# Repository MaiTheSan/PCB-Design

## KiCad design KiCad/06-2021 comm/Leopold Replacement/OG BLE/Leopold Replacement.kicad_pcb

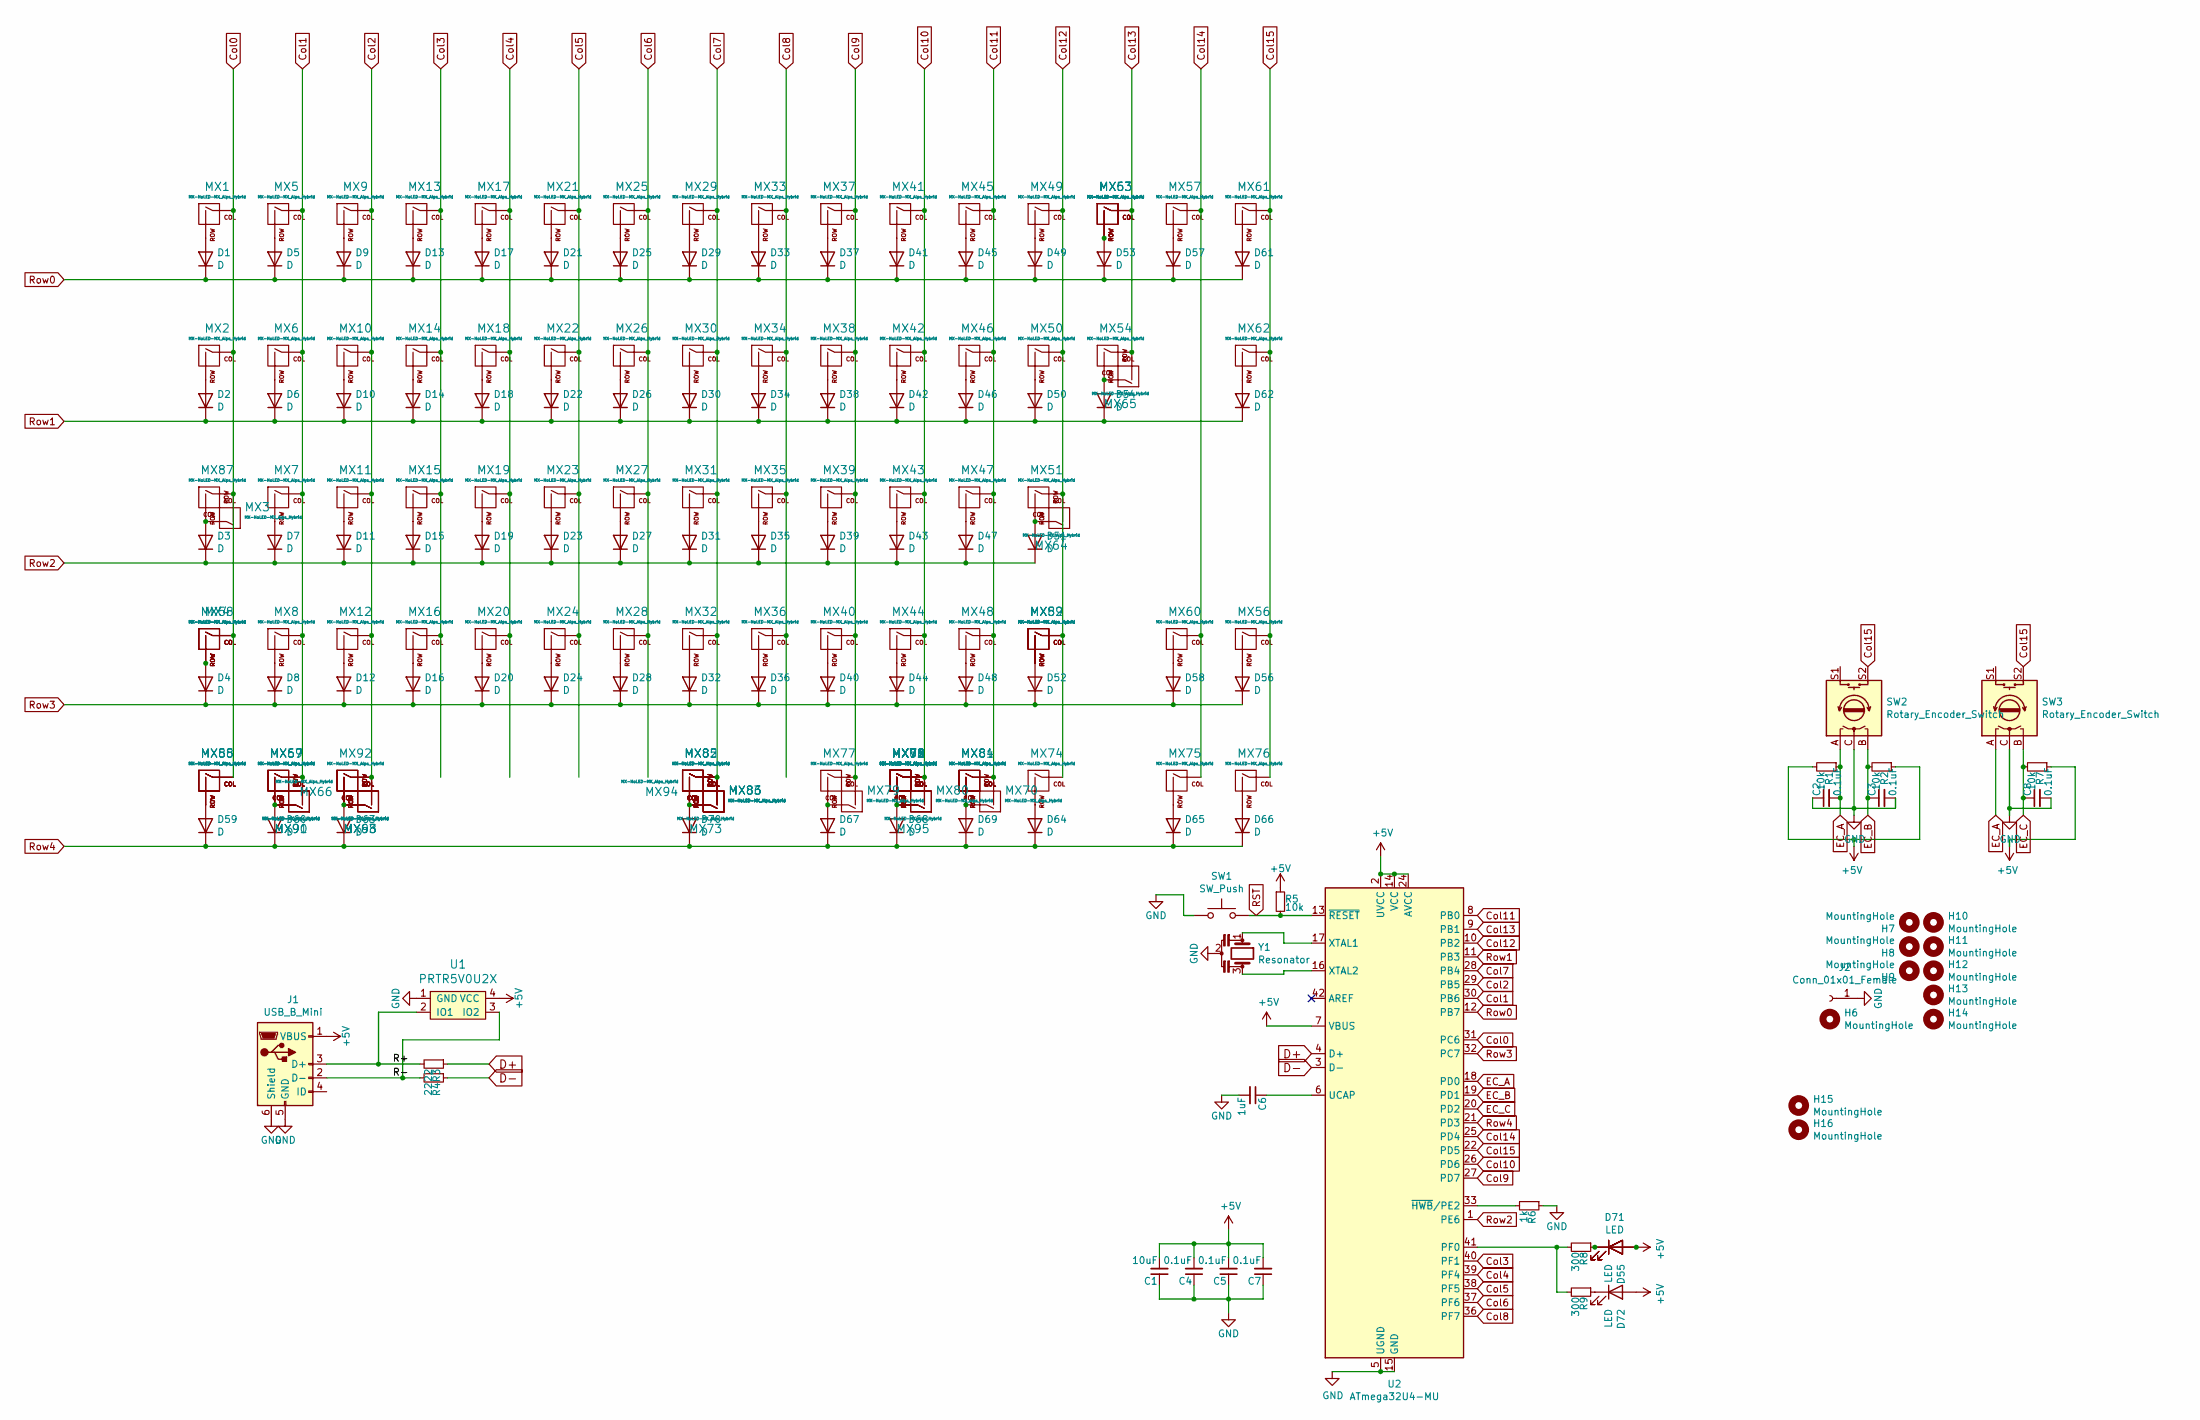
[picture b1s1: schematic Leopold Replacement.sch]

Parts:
C1: 10uF; C_0603
C2, C3, C4, C5, C7, C8: 0.1uF; C_0603
C6: 1uF; C_0603
D1, D2, D3, D4, D5, D6, D7, D8, D9, D10, D11, D12, D13, D14, D15, D16, D17, D18, D19, D20, D21, D22, D23, D24, D25, D26, D27, D28, D29, D30, D31, D32, D33, D34, D35, D36, D37, D38, D39, D40, D41, D42, D43, D44, D45, D46, D47, D48, D49, D50, D51, D52, D53, D54, D56, D57, D58, D59, D60, D61, D62, D63, D64, D65, D66, D67, D68, D69, D70: D; D_SOD-123
D55: LED; MXOnly-LEDONLY
D71: LED; MXOnly-LEDONLY-FLIPPED
D72: LED; MXOnly-LEDONLY-MID
H6: MountingHole; 10mm-Leopold-Mounting-Hole
H7, H8, H9, H10, H11, H12, H13, H14: MountingHole; Leopold-Mounting-Hole-Main
H15, H16: MountingHole; Leopold-mounting-hole-circle
J1: USB_B_Mini; Molex-0548190589
J2: Conn_01x01_Female; Leopold-Mounting-Hole
MX1, MX2, MX3, MX5, MX6, MX7, MX8, MX9, MX10, MX11, MX12, MX13, MX14, MX15, MX16, MX17, MX18, MX19, MX20, MX21, MX22, MX23, MX24, MX25, MX26, MX27, MX28, MX29, MX30, MX31, MX32, MX33, MX34, MX35, MX36, MX37, MX38, MX39, MX40, MX41, MX42, MX43, MX44, MX45, MX46, MX47, MX48, MX49, MX50, MX53, MX54, MX56, MX57, MX58, MX60, MX61, MX62, MX65, MX67, MX74, MX75, MX76, MX81, MX89, MX91: MX-NoLED-MX_Alps_Hybrid; Mx_Alps_100
MX4, MX51, MX52, MX64: MX-NoLED-MX_Alps_Hybrid; Mx_Alps_225
MX55, MX59, MX66, MX68, MX77, MX78, MX79, MX80, MX84, MX87: MX-NoLED-MX_Alps_Hybrid; Mx_Alps_125
MX63: MX-NoLED-MX_Alps_Hybrid; Mx_Alps_200
MX69, MX70, MX71, MX92, MX95: MX-NoLED-MX_Alps_Hybrid; ALPS-1.5U
MX72, MX88, MX93, MX96: MX-NoLED-MX_Alps_Hybrid; Mx_Alps_150
MX73, MX85: MX-NoLED-MX_Alps_Hybrid; ALPS-6.5U
MX82, MX83: MX-NoLED-MX_Alps_Hybrid; Mx_Alps_625_FL
MX86, MX94: MX-NoLED-MX_Alps_Hybrid; Mx_Alps_700_FL
MX90: MX-NoLED-MX_Alps_Hybrid; ALPS-1.25U
R1, R2, R5, R7: 10k; R_0805
R3, R4: 22; R_0603
R6: 1k; R_0805
R8, R9: 300; R_0805
SW1: SW_Push; SKQG-1155865
SW2, SW3: Rotary_Encoder_Switch; RotaryEncoder_Alps_EC11E-Switch_Vertical_H20mm_Center
U1: PRTR5V0U2X; SOT143B
U2: ATmega32U4-MU; QFN-44-1EP_7x7mm_P0.5mm_EP5.15x5.15mm
Y1: Resonator; Resonator_SMD_muRata_CSTxExxV-3Pin_3.0x1.1mm

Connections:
+5V: C1.2, C4.2, C5.2, C7.2, D55.2 (A), D71.2 (A), D72.2 (A), J1.1 (VBUS), R1.2, R2.1, R5.1, R7.1, U1.4 (VCC), U2.2 (UVCC), U2.7 (VBUS), U2.14 (VCC), U2.24 (AVCC), U2.34 (VCC), U2.44 (AVCC)
/R+: J1.3 (D+), R3.2, U1.2 (IO1)
/R-: J1.2 (D-), R4.2, U1.3 (IO2)
Col0: MX1.1 (COL), MX2.1 (COL), MX3.2 (ROW), MX4.1 (COL), MX55.1 (COL), MX58.1 (COL), MX87.1 (COL), MX88.1 (COL), U2.31 (PC6)
Col1: MX5.1 (COL), MX6.1 (COL), MX7.1 (COL), MX8.1 (COL), MX59.1 (COL), MX67.1 (COL), MX90.2 (ROW), MX91.2 (ROW), U2.30 (PB6)
Col2: MX9.1 (COL), MX10.1 (COL), MX11.1 (COL), MX12.1 (COL), MX66.1 (COL), MX68.2 (ROW), MX92.1 (COL), MX93.2 (ROW), U2.29 (PB5)
Col3: MX13.1 (COL), MX14.1 (COL), MX15.1 (COL), MX16.1 (COL), U2.40 (PF1)
Col4: MX17.1 (COL), MX18.1 (COL), MX19.1 (COL), MX20.1 (COL), U2.39 (PF4)
Col5: MX21.1 (COL), MX22.1 (COL), MX23.1 (COL), MX24.1 (COL), U2.38 (PF5)
Col6: MX25.1 (COL), MX26.1 (COL), MX27.1 (COL), MX28.1 (COL), U2.37 (PF6)
Col7: MX29.1 (COL), MX30.1 (COL), MX31.1 (COL), MX32.1 (COL), MX73.2 (ROW), MX82.1 (COL), MX83.2 (ROW), MX85.1 (COL), MX86.2 (ROW), MX94.1 (COL), U2.28 (PB4)
Col8: MX33.1 (COL), MX34.1 (COL), MX35.1 (COL), MX36.1 (COL), U2.36 (PF7)
Col9: MX37.1 (COL), MX38.1 (COL), MX39.1 (COL), MX40.1 (COL), MX77.1 (COL), MX79.2 (ROW), U2.27 (PD7)
Col10: MX41.1 (COL), MX42.1 (COL), MX43.1 (COL), MX44.1 (COL), MX69.1 (COL), MX71.1 (COL), MX72.1 (COL), MX78.1 (COL), MX80.2 (ROW), MX95.2 (ROW), MX96.1 (COL), U2.26 (PD6)
Col11: MX45.1 (COL), MX46.1 (COL), MX47.1 (COL), MX48.1 (COL), MX70.2 (ROW), MX81.1 (COL), MX84.1 (COL), U2.8 (PB0)
Col12: MX49.1 (COL), MX50.1 (COL), MX51.1 (COL), MX52.1 (COL), MX64.2 (ROW), MX74.1 (COL), MX89.1 (COL), U2.10 (PB2)
Col13: MX53.1 (COL), MX54.1 (COL), MX63.1 (COL), MX65.2 (ROW), U2.9 (PB1)
Col14: MX57.1 (COL), MX60.1 (COL), MX75.1 (COL), U2.25 (PD4)
Col15: MX56.1 (COL), MX61.1 (COL), MX62.1 (COL), MX76.1 (COL), SW2.S2, SW3.S2, U2.22 (PD5)
D+: R3.1, U2.4 (D+)
D-: R4.1, U2.3 (D-)
EC_A: C2.2, R1.1, SW2.A, SW3.A, U2.18 (PD0)
EC_B: C3.1, R2.2, SW2.B, U2.19 (PD1)
EC_C: C8.1, R7.2, SW3.B, U2.20 (PD2)
GND: C1.1, C2.1, C3.2, C4.1, C5.1, C6.2, C7.1, C8.2, J1.5 (GND), J1.6 (Shield), J2.1, R6.1, SW1.1, SW2.C, SW3.C, U1.1 (GND), U2.5 (UGND), U2.15 (GND), U2.23 (GND), U2.35 (GND), U2.43 (GND), U2.45 (GND), Y1.2
unnamed: C6.1, U2.6 (UCAP)
unnamed: D1.2 (A), MX1.2 (ROW)
unnamed: D2.2 (A), MX2.2 (ROW)
unnamed: D3.2 (A), MX3.1 (COL), MX87.2 (ROW)
unnamed: D4.2 (A), MX4.2 (ROW), MX58.2 (ROW)
unnamed: D5.2 (A), MX5.2 (ROW)
unnamed: D6.2 (A), MX6.2 (ROW)
unnamed: D7.2 (A), MX7.2 (ROW)
unnamed: D8.2 (A), MX8.2 (ROW)
unnamed: D9.2 (A), MX9.2 (ROW)
unnamed: D10.2 (A), MX10.2 (ROW)
unnamed: D11.2 (A), MX11.2 (ROW)
unnamed: D12.2 (A), MX12.2 (ROW)
unnamed: D13.2 (A), MX13.2 (ROW)
unnamed: D14.2 (A), MX14.2 (ROW)
unnamed: D15.2 (A), MX15.2 (ROW)
unnamed: D16.2 (A), MX16.2 (ROW)
unnamed: D17.2 (A), MX17.2 (ROW)
unnamed: D18.2 (A), MX18.2 (ROW)
unnamed: D19.2 (A), MX19.2 (ROW)
unnamed: D20.2 (A), MX20.2 (ROW)
unnamed: D21.2 (A), MX21.2 (ROW)
unnamed: D22.2 (A), MX22.2 (ROW)
unnamed: D23.2 (A), MX23.2 (ROW)
unnamed: D24.2 (A), MX24.2 (ROW)
unnamed: D25.2 (A), MX25.2 (ROW)
unnamed: D26.2 (A), MX26.2 (ROW)
unnamed: D27.2 (A), MX27.2 (ROW)
unnamed: D28.2 (A), MX28.2 (ROW)
unnamed: D29.2 (A), MX29.2 (ROW)
unnamed: D30.2 (A), MX30.2 (ROW)
unnamed: D31.2 (A), MX31.2 (ROW)
unnamed: D32.2 (A), MX32.2 (ROW)
unnamed: D33.2 (A), MX33.2 (ROW)
unnamed: D34.2 (A), MX34.2 (ROW)
unnamed: D35.2 (A), MX35.2 (ROW)
unnamed: D36.2 (A), MX36.2 (ROW)
unnamed: D37.2 (A), MX37.2 (ROW)
unnamed: D38.2 (A), MX38.2 (ROW)
unnamed: D39.2 (A), MX39.2 (ROW)
unnamed: D40.2 (A), MX40.2 (ROW)
unnamed: D41.2 (A), MX41.2 (ROW)
unnamed: D42.2 (A), MX42.2 (ROW)
unnamed: D43.2 (A), MX43.2 (ROW)
unnamed: D44.2 (A), MX44.2 (ROW)
unnamed: D45.2 (A), MX45.2 (ROW)
unnamed: D46.2 (A), MX46.2 (ROW)
unnamed: D47.2 (A), MX47.2 (ROW)
unnamed: D48.2 (A), MX48.2 (ROW)
unnamed: D49.2 (A), MX49.2 (ROW)
unnamed: D50.2 (A), MX50.2 (ROW)
unnamed: D51.2 (A), MX51.2 (ROW), MX64.1 (COL)
unnamed: D52.2 (A), MX52.2 (ROW), MX89.2 (ROW)
unnamed: D53.2 (A), MX53.2 (ROW), MX63.2 (ROW)
unnamed: D54.2 (A), MX54.2 (ROW), MX65.1 (COL)
unnamed: D55.1 (K), D71.1 (K), R8.1
unnamed: D56.2 (A), MX56.2 (ROW)
unnamed: D57.2 (A), MX57.2 (ROW)
unnamed: D58.2 (A), MX60.2 (ROW)
unnamed: D59.2 (A), MX55.2 (ROW), MX88.2 (ROW)
unnamed: D60.2 (A), MX59.2 (ROW), MX67.2 (ROW), MX90.1 (COL), MX91.1 (COL)
unnamed: D61.2 (A), MX61.2 (ROW)
unnamed: D62.2 (A), MX62.2 (ROW)
unnamed: D63.2 (A), MX66.2 (ROW), MX68.1 (COL), MX92.2 (ROW), MX93.1 (COL)
unnamed: D64.2 (A), MX74.2 (ROW)
unnamed: D65.2 (A), MX75.2 (ROW)
unnamed: D66.2 (A), MX76.2 (ROW)
unnamed: D67.2 (A), MX77.2 (ROW), MX79.1 (COL)
unnamed: D68.2 (A), MX69.2 (ROW), MX71.2 (ROW), MX72.2 (ROW), MX78.2 (ROW), MX80.1 (COL), MX95.1 (COL), MX96.2 (ROW)
unnamed: D69.2 (A), MX70.1 (COL), MX81.2 (ROW), MX84.2 (ROW)
unnamed: D70.2 (A), MX73.1 (COL), MX82.2 (ROW), MX83.1 (COL), MX85.2 (ROW), MX86.1 (COL), MX94.2 (ROW)
unnamed: D72.1 (K), R9.1
unnamed: R6.2, U2.33 (~HWB~/PE2)
unnamed: R8.2, R9.2, U2.41 (PF0)
unnamed: U2.16 (XTAL2), Y1.3
unnamed: U2.17 (XTAL1), Y1.1
RST: R5.2, SW1.2, U2.13 (~RESET)
Row0: D1.1 (K), D5.1 (K), D9.1 (K), D13.1 (K), D17.1 (K), D21.1 (K), D25.1 (K), D29.1 (K), D33.1 (K), D37.1 (K), D41.1 (K), D45.1 (K), D49.1 (K), D53.1 (K), D57.1 (K), D61.1 (K), U2.12 (PB7)
Row1: D2.1 (K), D6.1 (K), D10.1 (K), D14.1 (K), D18.1 (K), D22.1 (K), D26.1 (K), D30.1 (K), D34.1 (K), D38.1 (K), D42.1 (K), D46.1 (K), D50.1 (K), D54.1 (K), D62.1 (K), U2.11 (PB3)
Row2: D3.1 (K), D7.1 (K), D11.1 (K), D15.1 (K), D19.1 (K), D23.1 (K), D27.1 (K), D31.1 (K), D35.1 (K), D39.1 (K), D43.1 (K), D47.1 (K), D51.1 (K), U2.1 (PE6)
Row3: D4.1 (K), D8.1 (K), D12.1 (K), D16.1 (K), D20.1 (K), D24.1 (K), D28.1 (K), D32.1 (K), D36.1 (K), D40.1 (K), D44.1 (K), D48.1 (K), D52.1 (K), D56.1 (K), D58.1 (K), U2.32 (PC7)
Row4: D59.1 (K), D60.1 (K), D63.1 (K), D64.1 (K), D65.1 (K), D66.1 (K), D67.1 (K), D68.1 (K), D69.1 (K), D70.1 (K), U2.21 (PD3)

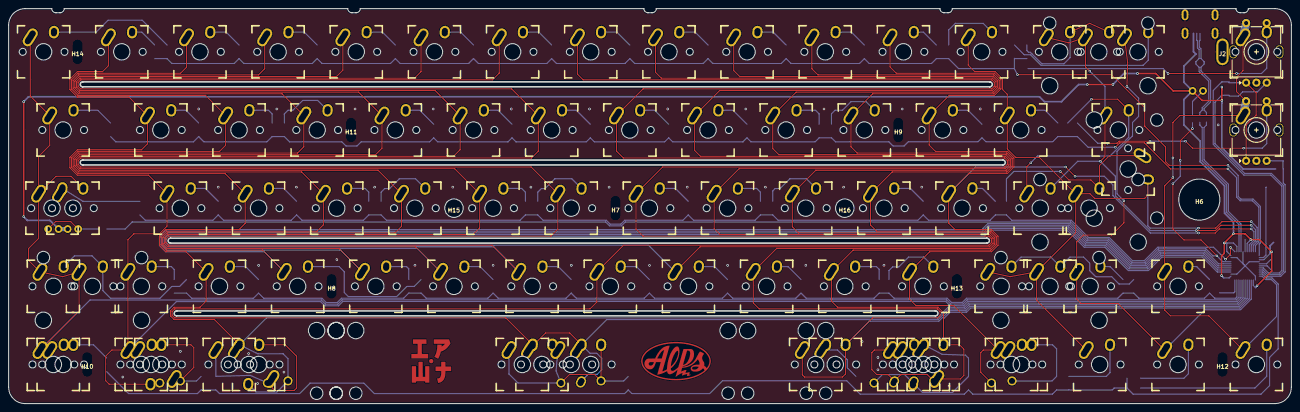
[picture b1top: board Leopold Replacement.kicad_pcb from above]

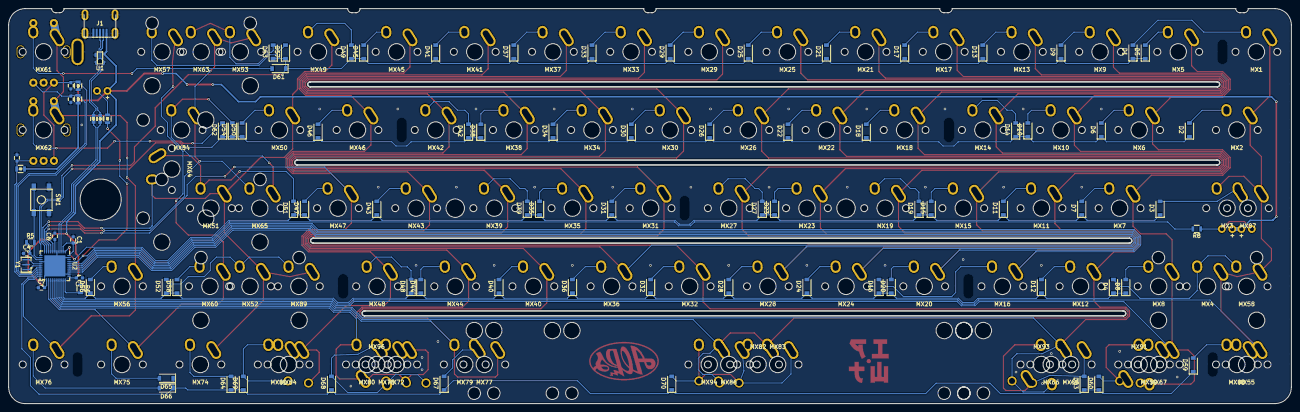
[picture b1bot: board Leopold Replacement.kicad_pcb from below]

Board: 2 copper layers, 312.0 x 96.1 mm, 204 parts (91 on the bottom side), 107 nets.

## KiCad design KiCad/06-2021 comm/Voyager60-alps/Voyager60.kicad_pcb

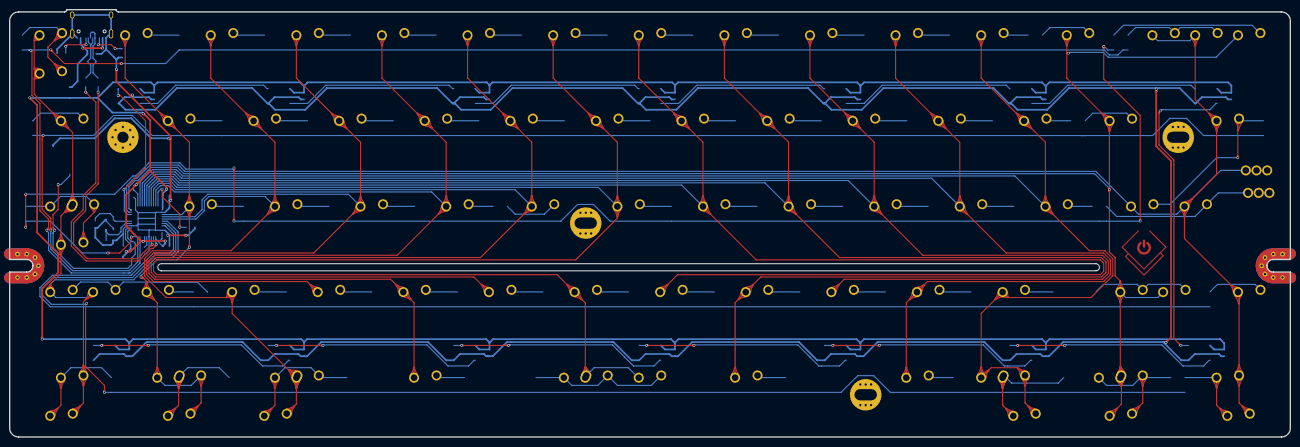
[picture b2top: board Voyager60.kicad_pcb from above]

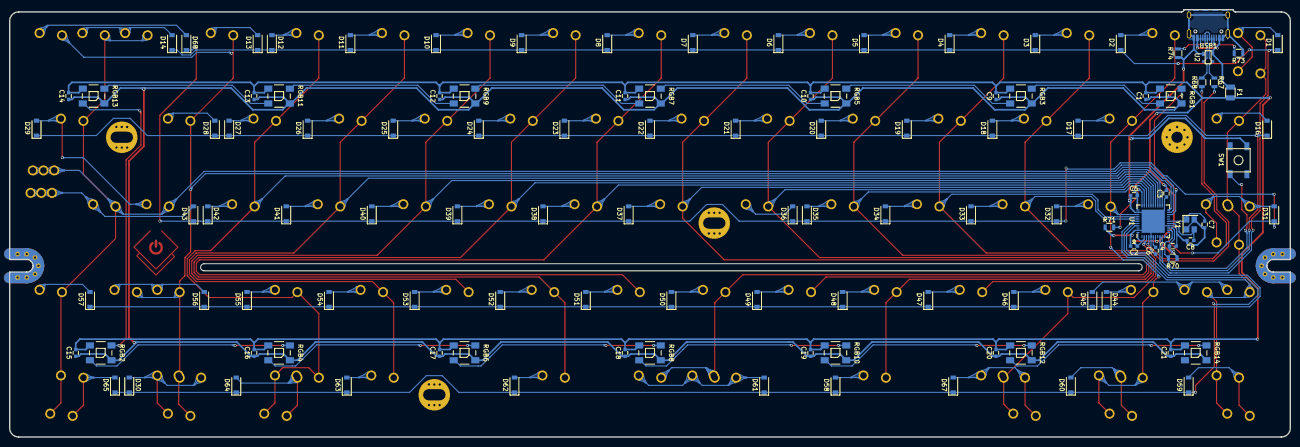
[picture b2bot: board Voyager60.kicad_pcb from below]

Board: 2 copper layers, 285.0 x 95.1 mm, 201 parts (113 on the bottom side), 113 nets.

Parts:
C1, C3, C4, C5, C9, C10, C11, C12, C13, C14, C15, C16, C17, C18, C19, C20, C21: 0.1uF; C_0603
C2: 10uF; C_0603
C6: 1uF; C_0603
C7, C8: 22pF; C_0603
D1, D2, D3, D4, D5, D6, D7, D8, D9, D10, D11, D12, D13, D14, D16, D17, D18, D19, D20, D21, D22, D23, D24, D25, D26, D27, D28, D29, D30, D31, D32, D33, D34, D35, D36, D37, D38, D39, D40, D41, D42, D43, D44, D45, D46, D47, D48, D49, D50, D51, D52, D53, D54, D55, D56, D57, D58, D59, D60, D61, D62, D63, D64, D65, D67, D68: SOD-123; D_SOD-123
F1: 500mA; Fuse_SMD1206_Reflow
K_#1, K_#2, K_#3, K_#4, K_#5, K_#6, K_#7, K_#8, K_#9, K_#10: MX-1U; ALPS-1U
K_'1: MX-1U; ALPS-1U
K_,1: MX-1U; ALPS-1U
K_-1: MX-1U; ALPS-1U
K_.1: MX-1U; ALPS-1U
K_/1: MX-1U; ALPS-1U
K_;1: MX-1U; ALPS-1U
K_=1: MX-1U; ALPS-1U
K_A1: MX-1U; ALPS-1U
K_ALT1: MX-1.25U; ALPS-1.25U
K_ALT2, K_ALT3: MX-1.5U; ALPS-1.5U
K_B1: MX-1U; ALPS-1U
K_BACK1: MX-2U; ALPS-2U
K_C1: MX-1U; ALPS-1U
K_CAPS1: MX-1.75U; ALPS-1.75U
K_CAPS2: MX-1.25U; ALPS-1.25U
K_CAPS3: MX-1.5U; ALPS-1.5U
K_CTRL1: MX-1.25U; ALPS-1.25U
K_CTRL2: MX-1.5U; ALPS-1.5U
K_D1: MX-1U; ALPS-1U
K_E1: MX-1U; ALPS-1U
K_ENTER1: MX-2.25U; ALPS-2.25U
K_ENTER2, K_ENTER3, K_ENTER4: MX-1U; ALPS-1U
K_ESC1, K_ESC2: MX-1U; ALPS-1U
K_F1: MX-1U; ALPS-1U
K_G1: MX-1U; ALPS-1U
K_H1: MX-1U; ALPS-1U
K_I1: MX-1U; ALPS-1U
K_J1: MX-1U; ALPS-1U
K_K1: MX-1U; ALPS-1U
K_L1: MX-1U; ALPS-1U
K_M1: MX-1U; ALPS-1U
K_N1: MX-1U; ALPS-1U
K_O1: MX-1U; ALPS-1U
K_P1: MX-1U; ALPS-1U
K_Q1: MX-1U; ALPS-1U
K_R1: MX-1U; ALPS-1U
K_RALT1, K_RALT3: MX-1.5U; ALPS-1.5U
K_RALT2: MX-1.25U; ALPS-1.25U
K_RCTRL2: MX-1.25U; ALPS-1.25U
K_RCTRL3: MX-1.5U; ALPS-1.5U
K_RMENU2: MX-1.25U; ALPS-1.25U
K_RSHIFT1: MX-2.75U; ALPS-2.75U
K_RWIN1, K_RWIN2: MX-1.25U; ALPS-1.25U
K_RWIN3: MX-1U; ALPS-1U
K_S1: MX-1U; ALPS-1U
K_SBACK1, K_SBACK2: MX-1U; ALPS-1U
K_SHIFT1: MX-2.25U; ALPS-2.25U
K_SHIFT2: MX-1.25U; ALPS-1.25U
K_SHIFT3: MX-1U; ALPS-1U
K_SPACE1: MX-7U; ALPS-7U
K_SPACE2: MX-6.25U; ALPS-6.25U
K_SPACE3: MX-2.25U; ALPS-2.25U
K_SPACE4: MX-2.75U; ALPS-2.75U
K_SPACE5: MX-1.25U; ALPS-1.25U
K_SRSHIFT1: MX-1.75U; ALPS-1.75U
K_SRSHIFT2: MX-1U; ALPS-1U
K_T1: MX-1U; ALPS-1U
K_TAB1: MX-1.5U; ALPS-1.5U
K_U1: MX-1U; ALPS-1U
K_V1: MX-1U; ALPS-1U
K_W1: MX-1U; ALPS-1U
K_WIN1, K_WIN3: MX-1.25U; ALPS-1.25U
K_WIN2: MX-1U; ALPS-1U
K_X1: MX-1U; ALPS-1U
K_Y1: MX-1U; ALPS-1U
K_Z1: MX-1U; ALPS-1U
K_[1: MX-1U; ALPS-1U
K_\1: MX-1.5U; ALPS-1.5U
K_\2: MX-1U; ALPS-1U
K_]1: MX-1U; ALPS-1U
R67, R68: 22; R_0805
R70: 10k; R_0805
R71: 1k; R_0805
R73, R74: 5.1k; R_0805
RGB1, RGB2, RGB3, RGB4, RGB5, RGB6, RGB7, RGB8, RGB9, RGB10, RGB11, RGB12, RGB13, RGB14: WS2812B
SW1: 5.2x5.2mm; SKQG-1155865
U1: ATmega32U4-MU; QFN-44-1EP_7x7mm_Pitch0.5mm
U2: PRTR5V0U2X; SOT143B
USB1: HRO-TYPE-C-31-M-12; HRO-TYPE-C-31-M-12-Assembly
Y1: 16Mhz; Crystal_SMD_3225-4pin_3.2x2.5mm

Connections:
+5V: C1.2, C2.2, C3.2, C4.2, C5.2, C9.2, C10.2, C11.2, C12.2, C13.2, C14.2, C15.2, C16.2, C17.2, C18.2, C19.2, C20.2, C21.2, F1.1, R70.1, RGB1.1, RGB2.1, RGB3.1, RGB4.1, RGB5.1, RGB6.1, RGB7.1, RGB8.1, RGB9.1, RGB10.1, RGB11.1, RGB12.1, RGB13.1, RGB14.1, U1.2, U1.7, U1.14, U1.24, U1.34, U1.44
COL0: K_CAPS1.1, K_CAPS2.2, K_CAPS3.2, K_CTRL1.1, K_CTRL2.2, K_ESC1.1, K_ESC2.2, K_SHIFT1.1, K_SHIFT2.1, K_TAB1.1, U1.39
COL1: K_#1.1, K_A1.1, K_Q1.1, K_SHIFT3.1, K_WIN1.1, K_WIN2.1, K_WIN3.2, U1.36
COL2: K_#2.1, K_ALT1.1, K_ALT2.2, K_ALT3.1, K_S1.1, K_W1.1, K_Z1.1, U1.38
COL3: K_#3.1, K_D1.1, K_E1.1, K_X1.1, U1.37
COL4: K_#4.1, K_C1.1, K_F1.1, K_R1.1, K_SPACE3.1, U1.32
COL5: K_#5.1, K_G1.1, K_T1.1, K_V1.1, U1.31
COL6: K_#6.1, K_B1.1, K_H1.1, K_SPACE1.1, K_SPACE2.1, K_SPACE5.2, K_Y1.1, U1.30
COL7: K_#7.1, K_J1.1, K_N1.1, K_U1.1, U1.29
COL8: K_#8.1, K_I1.1, K_K1.1, K_M1.1, K_SPACE4.1, U1.28
COL9: K_#9.1, K_,1.1, K_L1.1, K_O1.1, U1.27
COL10: K_#10.1, K_.1.1, K_;1.1, K_P1.1, K_RALT2.1, U1.26
COL11: K_'1.1, K_-1.1, K_/1.1, K_RALT1.1, K_RALT3.2, K_RWIN2.1, K_[1.1, U1.25
COL12: K_=1.1, K_RMENU2.1, K_RSHIFT1.1, K_RWIN1.2, K_RWIN3.2, K_SBACK2.1, K_SRSHIFT1.1, K_]1.1, U1.22
COL13: K_BACK1.1, K_ENTER1.1, K_ENTER2.1, K_ENTER3.1, K_ENTER4.1, K_RCTRL2.1, K_RCTRL3.2, K_SBACK1.1, K_SRSHIFT2.1, K_\1.1, K_\2.1, U1.21
D+: R68.1, U1.4
D-: R67.1, U1.3
GND: C1.1, C2.1, C3.1, C4.1, C5.1, C6.2, C7.2, C8.2, C9.1, C10.1, C11.1, C12.1, C13.1, C14.1, C15.1, C16.1, C17.1, C18.1, C19.1, C20.1, C21.1, R71.1, R73.1, R74.1, RGB1.3, RGB2.3, RGB3.3, RGB4.3, RGB5.3, RGB6.3, RGB7.3, RGB8.3, RGB9.3, RGB10.3, RGB11.3, RGB12.3, RGB13.3, RGB14.3, SW1.1, U1.5, U1.15, U1.23, U1.35, U1.43, U1.45, U2.1, USB1.1, USB1.12, USB1.13, Y1.2, Y1.4
unnamed: C6.1, U1.6
unnamed: C7.1, U1.17, Y1.1
unnamed: C8.1, U1.16, Y1.3
unnamed: D1.2, K_ESC1.2, K_ESC2.1
unnamed: D2.2, K_#1.2
unnamed: D3.2, K_#2.2
unnamed: D4.2, K_#3.2
unnamed: D5.2, K_#4.2
unnamed: D6.2, K_#5.2
unnamed: D7.2, K_#6.2
unnamed: D8.2, K_#7.2
unnamed: D9.2, K_#8.2
unnamed: D10.2, K_#9.2
unnamed: D11.2, K_#10.2
unnamed: D12.2, K_-1.2
unnamed: D13.2, K_=1.2
unnamed: D14.2, K_BACK1.2, K_SBACK1.2
unnamed: D16.2, K_TAB1.2
unnamed: D17.2, K_Q1.2
unnamed: D18.2, K_W1.2
unnamed: D19.2, K_E1.2
unnamed: D20.2, K_R1.2
unnamed: D21.2, K_T1.2
unnamed: D22.2, K_Y1.2
unnamed: D23.2, K_U1.2
unnamed: D24.2, K_I1.2
unnamed: D25.2, K_O1.2
unnamed: D26.2, K_P1.2
unnamed: D27.2, K_[1.2
unnamed: D28.2, K_]1.2
unnamed: D29.2, K_\1.2, K_\2.2
unnamed: D30.2, K_RMENU2.2, K_RWIN1.1, K_RWIN3.1
unnamed: D31.2, K_CAPS1.2, K_CAPS2.1, K_CAPS3.1
unnamed: D32.2, K_A1.2
unnamed: D33.2, K_S1.2
unnamed: D34.2, K_D1.2
unnamed: D35.2, K_F1.2
unnamed: D36.2, K_G1.2
unnamed: D37.2, K_H1.2
unnamed: D38.2, K_J1.2
unnamed: D39.2, K_K1.2
unnamed: D40.2, K_L1.2
unnamed: D41.2, K_;1.2
unnamed: D42.2, K_'1.2
unnamed: D43.2, K_ENTER1.2, K_ENTER2.2, K_ENTER3.2, K_ENTER4.2
unnamed: D44.2, K_SHIFT3.2
unnamed: D45.2, K_SHIFT1.2, K_SHIFT2.2
unnamed: D46.2, K_Z1.2
unnamed: D47.2, K_X1.2
unnamed: D48.2, K_C1.2
unnamed: D49.2, K_V1.2
unnamed: D50.2, K_B1.2
unnamed: D51.2, K_N1.2
unnamed: D52.2, K_M1.2
unnamed: D53.2, K_,1.2
unnamed: D54.2, K_.1.2
unnamed: D55.2, K_/1.2
unnamed: D56.2, K_RSHIFT1.2, K_SRSHIFT1.2
unnamed: D57.2, K_SRSHIFT2.2
unnamed: D58.2, K_SPACE3.2
unnamed: D59.2, K_CTRL1.2, K_CTRL2.1
unnamed: D60.2, K_WIN1.2, K_WIN2.2, K_WIN3.1
unnamed: D61.2, K_SPACE1.2, K_SPACE2.2, K_SPACE5.1
unnamed: D62.2, K_SPACE4.2
unnamed: D63.2, K_RALT2.2
unnamed: D64.2, K_RALT1.2, K_RALT3.1, K_RWIN2.2
unnamed: D65.2, K_RCTRL2.2, K_RCTRL3.1
unnamed: D67.2, K_ALT1.2, K_ALT2.1, K_ALT3.2
unnamed: D68.2, K_SBACK2.2
unnamed: R67.2, U2.3, USB1.5, USB1.7
unnamed: R68.2, U2.2, USB1.6, USB1.8
unnamed: R70.2, SW1.2, U1.13
unnamed: R71.2, U1.33
unnamed: R73.2, USB1.4
unnamed: R74.2, USB1.10
unnamed: RGB1.2, RGB3.4
unnamed: RGB2.2, RGB4.4
unnamed: RGB3.2, RGB5.4
unnamed: RGB4.2, RGB6.4
unnamed: RGB5.2, RGB7.4
unnamed: RGB6.2, RGB8.4
unnamed: RGB7.2, RGB9.4
unnamed: RGB10.2, RGB12.4
unnamed: RGB8.2, RGB10.4
unnamed: RGB11.2, RGB13.4
unnamed: RGB9.2, RGB11.4
unnamed: RGB12.2, RGB14.4
unnamed: RGB2.4, RGB13.2
RGBLED: RGB1.4, U1.20
ROW0: D1.1, D2.1, D3.1, D4.1, D5.1, D6.1, D7.1, D8.1, D9.1, D10.1, D11.1, D12.1, D13.1, D14.1, U1.9
ROW1: D16.1, D17.1, D18.1, D19.1, D20.1, D21.1, D22.1, D23.1, D24.1, D25.1, D26.1, D27.1, D28.1, D29.1, U1.10
ROW2: D31.1, D32.1, D33.1, D34.1, D35.1, D36.1, D37.1, D38.1, D39.1, D40.1, D41.1, D42.1, D43.1, D68.1, U1.11
ROW3: D44.1, D45.1, D46.1, D47.1, D48.1, D49.1, D50.1, D51.1, D52.1, D53.1, D54.1, D55.1, D56.1, D57.1, U1.41
ROW4: D30.1, D58.1, D59.1, D60.1, D61.1, D62.1, D63.1, D64.1, D65.1, D67.1, U1.40
VCC: F1.2, U2.4, USB1.2, USB1.11
